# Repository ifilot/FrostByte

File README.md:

# FrostByte iCE FPGA Programmer

Firmware for a Raspberry Pi Pico that programs an external SPI flash used to
configure an iCE FPGA. The Pico exposes a USB CDC serial interface to the host,
holds the FPGA in reset while the flash is accessed, and speaks SPI to the flash.

The current source targets a W25Q16-style SPI flash and an iCE40UP5K-style FPGA
reset/done interface.

## Hardware Connections

Default pin assignments are in `src/constants.h`.

| Pico GPIO | Signal | Notes |
| --- | --- | --- |
| GP16 | SPI MISO | Flash DO |
| GP17 | SPI CS | Flash `/CS` |
| GP18 | SPI SCK | Flash CLK |
| GP19 | SPI MOSI | Flash DI |
| GP14 | CDONE | FPGA configuration done input |
| GP15 | CRESET | FPGA reset output, active low |
| GP25 | LED | Pico on-board LED |

The firmware starts with `CRESET` low, so the FPGA is held in reset while flash
commands are sent.

## Build

Install the Raspberry Pi Pico SDK and the ARM embedded GCC toolchain first. This
project's `src/CMakeLists.txt` currently expects the SDK at `/opt/pico-sdk` and
defaults to `PICO_BOARD=pico2` for Raspberry Pi Pico 2 / RP2350.

From the repository root:

```sh
cmake -S src -B build -j
cmake --build build -j
```

If your SDK does not have `picotool` installed and your build machine cannot
download it, disable picotool post-processing:

```sh
cmake -S src -B build -DPICO_NO_PICOTOOL=1
cmake --build build
```

To build for an original RP2040 Pico instead, configure with
`-DPICO_BOARD=pico`.

With picotool available, the normal build produces a UF2 file:

```text
build/frostbyte.uf2
```

With `PICO_NO_PICOTOOL=1`, the build still produces:

```text
build/frostbyte.elf
build/frostbyte.bin
build/frostbyte.hex
```

## Flash The Pico

1. Hold the Pico BOOTSEL button while connecting USB.
2. Copy `build/frostbyte.uf2` to the `RPI-RP2` mass-storage device.
3. Reconnect the Pico normally.
4. Open the new USB serial port.

On Linux the serial device is usually `/dev/ttyACM0`. On macOS it is usually
under `/dev/tty.usbmodem*`. On Windows it appears as a COM port.

## Program The FPGA Flash

The host-side programming script is `scripts/writefpga.py`. It talks to FrostByte
over USB CDC serial, keeps the FPGA in reset while accessing the SPI flash,
programs the ROM, verifies the written data by reading it back, then releases
the FPGA and checks CDONE.

Install the Python serial dependency if needed:

```sh
python -m pip install pyserial
```

From the repository root, program the default known-good ROM:

```sh
python scripts/writefpga.py
```

The default ROM is:

```text
rom/VERA_48.0.1.BIN
```

That file is 104,169 bytes, so the script erases two 64 KiB blocks, writes 26
4 KiB sectors, and verifies every written 256-byte page. The final partial
sector is padded with `0xFF`, matching the erased flash state.

Useful options:

```sh
python scripts/writefpga.py --port COM16
python scripts/writefpga.py --port /dev/ttyACM0
python scripts/writefpga.py path/to/other.bin
python scripts/writefpga.py --no-boot
```

A successful run should include these confirmations:

```text
Programmer ID: FROSTBYTE-v0.1.0
Flash JEDEC ID: EF 40 15
FPGA held in reset: CRESET low
Verified erased block 00
Verified erased block 01
Flash and verification completed successfully
FPGA boot confirmed: CDONE is high
```

What this proves:

- The FrostByte firmware responded over serial.
- The flash identified as the expected W25Q16-style device.
- The FPGA was held in reset while the flash was modified.
- The affected erase blocks were blank after erase.
- Every written page read back byte-for-byte against the ROM file.
- `BOOTFPGA` released `CRESET` and CDONE read high after configuration.

The script's CDONE check confirms the post-configuration value. It does not
currently sample CDONE while `CRESET` is low; add a firmware command for that if
a full low-to-high CDONE transition test is needed later.

## Serial Protocol

Commands are fixed-width 8-byte ASCII words. The firmware accepts only uppercase
letters `A` through `Z` and digits `0` through `9`; all other characters are
ignored. Every recognized or unrecognized 8-byte word is echoed back before any
command response.

Multi-byte numeric fields are ASCII hexadecimal. Binary responses are raw bytes,
not printable text.

| Command | Extra host data | Response after echo | Meaning |
| --- | --- | --- | --- |
| `READINFO` | none | 16 ASCII bytes | Board ID, currently `FROSTBYTE-v0.1.0` |
| `DEVIDSST` | none | 3 raw bytes | Flash JEDEC ID |
| `ERASBKxx` | none | 1 raw byte | Erase 64 KiB block `0xxx0000`; response is the block byte |
| `CHCKBKxx` | none | 1 raw byte | Check block erased; `0x00` means erased, `0xFF` means not erased |
| `RDPGxxxx` | none | 256 raw bytes | Read 256-byte page `0xxxxx` |
| `WRSECTxx` | 4096 raw bytes | 2 raw bytes | Write 4096-byte sector `xx`; response is CRC16/XMODEM, low byte first |
| `RESETCHP` | none | none | Send flash reset sequence |
| `HOLDFPGA` | none | 1 raw byte | Hold FPGA in reset; response is `0x00` |
| `BOOTFPGA` | none | 1 raw byte | Release FPGA reset; response is `0x01` if CDONE is high, else `0x00` |

Example: read the JEDEC ID with Python.

```python
import serial

with serial.Serial("/dev/ttyACM0", 115200, timeout=1) as port:
    port.write(b"DEVIDSST")
    echo = port.read(8)
    jedec = port.read(3)
    print(echo, jedec.hex(" "))
```

Example: write one 4096-byte sector.

```python
import serial

sector = 0x00
payload = bytes([0xFF]) * 4096

with serial.Serial("/dev/ttyACM0", 115200, timeout=5) as port:
    port.write(f"WRSECT{sector:02X}".encode("ascii"))
    echo = port.read(8)
    port.write(payload)
    crc = port.read(2)
    print(echo, crc.hex(" "))
```

## Typical Programming Flow

This is the flow implemented by `scripts/writefpga.py`:

1. Send `READINFO` and confirm the FrostByte firmware responds.
2. Send `HOLDFPGA` to hold the FPGA in reset.
3. Send `RESETCHP`.
4. Send `DEVIDSST` and confirm the expected flash responds.
5. Erase every 64 KiB block that will contain the FPGA bitstream with
   `ERASBKxx`.
6. Verify each erased block with `CHCKBKxx`.
7. Send `WRSECTxx` for each 4096-byte chunk of the bitstream and check the
   returned CRC16/XMODEM.
8. Verify by reading pages back with `RDPGxxxx`.
9. Send `BOOTFPGA` and check for a `0x01` CDONE response.

## Known Limitations

- `WRSECTxx` accepts only an 8-bit sector index. A W25Q16 is 2 MiB, which is
  512 sectors of 4096 bytes, so the current protocol can address only sectors
  `0x00` through `0xFF`.
- The firmware allocates a full 4096-byte sector buffer on the stack in
  `flash_write_sector()`. The Pico SDK default RP2040 stack is 2048 bytes, so
  writes may corrupt memory unless the buffer is moved to static storage, written
  page-by-page, or the stack size is increased.
- `flash_wait_busy()` stops waiting after 1000 ms and does not report timeout
  failure to the caller. Some 64 KiB block erases can take longer than that.
- Malformed hexadecimal fields are not rejected. For example, `ERASBKGG` is
  parsed by `strtoul()` as zero and may erase block `0x00`.
- Unknown commands are echoed but do not return an error byte, so host software
  should not wait indefinitely for a response unless it knows the command has
  one.

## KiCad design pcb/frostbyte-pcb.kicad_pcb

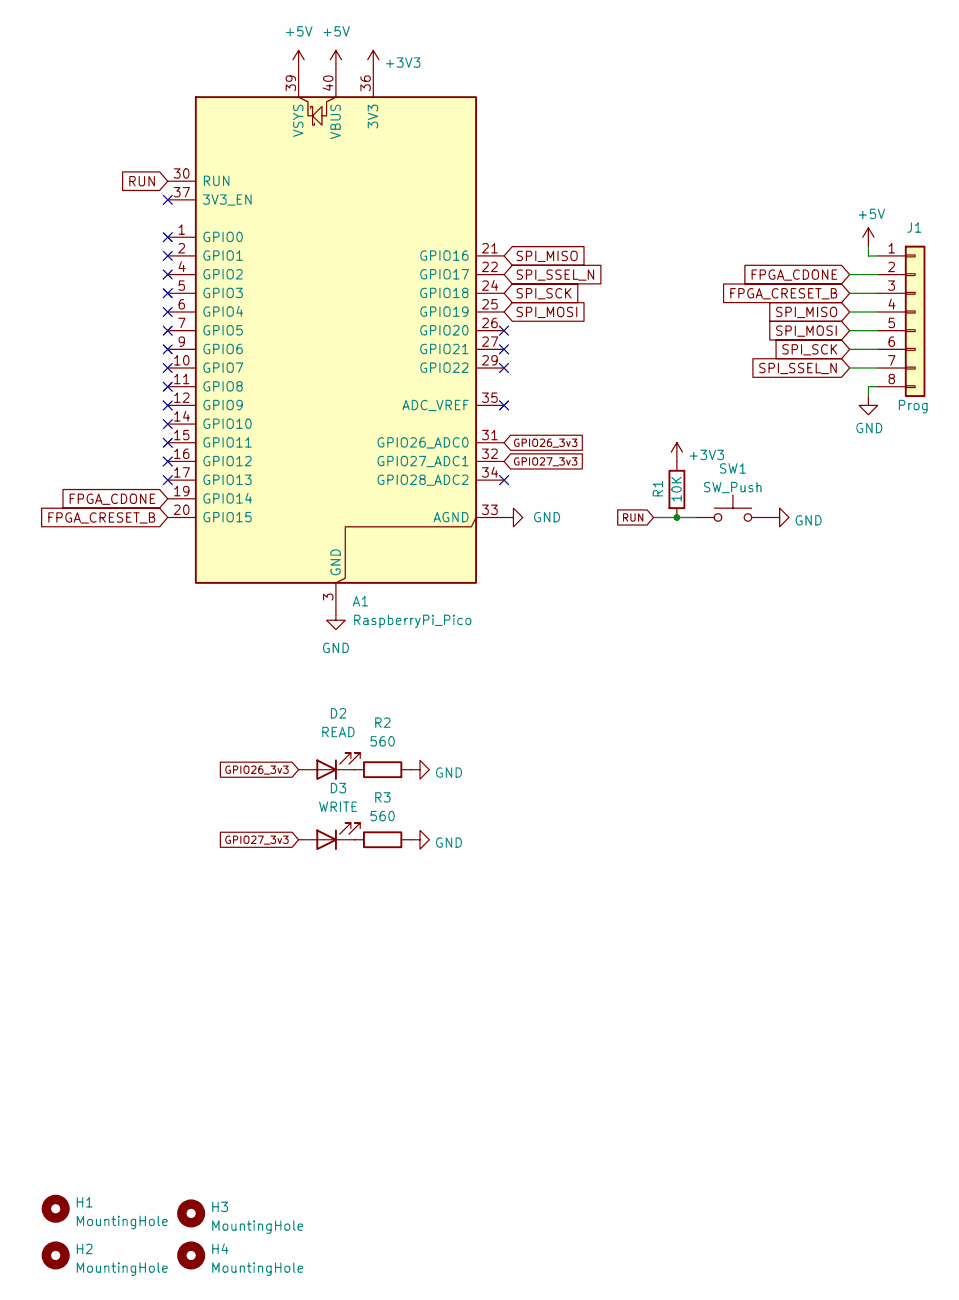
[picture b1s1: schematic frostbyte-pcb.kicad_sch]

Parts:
A1: RaspberryPi_Pico; RaspberryPi_Pico_Common_Unspecified
D2: READ; LED_D5.0mm
D3: WRITE; LED_D5.0mm
H1, H2, H3, H4: MountingHole; MountingHole_3.2mm_M3
J1: Prog; PinHeader_1x08_P2.54mm_Vertical
R1: 10K; R_Axial_DIN0207_L6.3mm_D2.5mm_P7.62mm_Horizontal; LCSC C17414
R2, R3: 560; R_Axial_DIN0207_L6.3mm_D2.5mm_P7.62mm_Horizontal; LCSC C28636
SW1: SW_Push; SW_PUSH_6mm

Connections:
+3V3: A1.36 (3V3), R1.1
+5V: A1.39 (VSYS), A1.40 (VBUS), J1.1
FPGA_CDONE: A1.19 (GPIO14), J1.2
FPGA_CRESET_B: A1.20 (GPIO15), J1.3
GND: A1.3 (GND), A1.8 (GND), A1.13 (GND), A1.18 (GND), A1.23 (GND), A1.28 (GND), A1.33 (AGND), A1.38 (GND), J1.8, R2.2, R3.2, SW1.2
GPIO26_3v3: A1.31 (GPIO26_ADC0), D2.2 (A)
GPIO27_3v3: A1.32 (GPIO27_ADC1), D3.2 (A)
unnamed: D2.1 (K), R2.1
unnamed: D3.1 (K), R3.1
RUN: A1.30 (RUN), R1.2, SW1.1
SPI_MISO: A1.21 (GPIO16), J1.4
SPI_MOSI: A1.25 (GPIO19), J1.5
SPI_SCK: A1.24 (GPIO18), J1.6
SPI_SSEL_N: A1.22 (GPIO17), J1.7

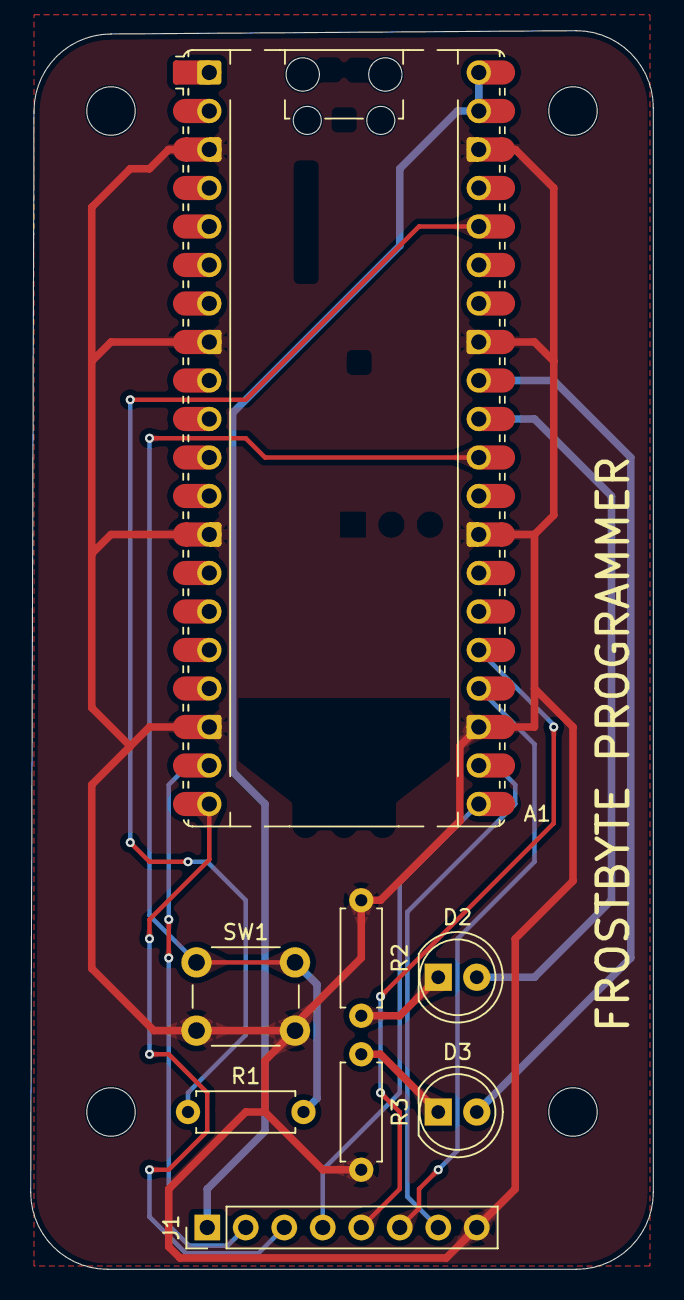
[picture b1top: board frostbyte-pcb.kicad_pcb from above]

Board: 2 copper layers, 41.1 x 81.7 mm, 12 parts (0 on the bottom side), 14 nets.

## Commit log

2026-06-11 Removing bytecode
2026-06-11 Adding flasher PCB
2026-06-12 Creating PCB
